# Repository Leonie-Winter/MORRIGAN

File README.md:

# MORRIGAN
--- 
## What is Morrigan?

Morrigan stands for 
- **M**obile
- **O**ptimized
- **R**eal-time
- **R**essource 
- **I**nterface
- **G**auge
- **A**nalysis
- **N**etwork

and aims to be a simple-to-use device based on the Raspberry Pi 3 to determine the quality of water using sensors from Gravity.

It measures the `total dissolved solids (TDS)(that are conductive), the dissolved oxygen (DO), the temperature, the pH, and the Turbidity`

---
You will find a build log in the [wiki](https://github.com/Leonie-Winter/MORRIGAN/wiki/build_log)[WIP] to find out how to get started

`/src` includes all files for the actual code and `/models` which includes a custom pcb design and a 3d case

 &nbsp;&nbsp;&nbsp;&nbsp;&nbsp;

--- 

If you are interested in thins such as previous competitions,the costs, and how it works check out the [wiki](https://github.com/Leonie-Winter/MORRIGAN/wiki/)

---

**This project was funded by the Erasmus+ program of the European Union.**
Funded by the European Union. Views and opinions expressed are however those of the author(s) only and do not necessarily reflect those of the European Union or the European Education and Culture Executive Agency (EACEA). Neither the European Union nor EACEA can be held responsible for them.

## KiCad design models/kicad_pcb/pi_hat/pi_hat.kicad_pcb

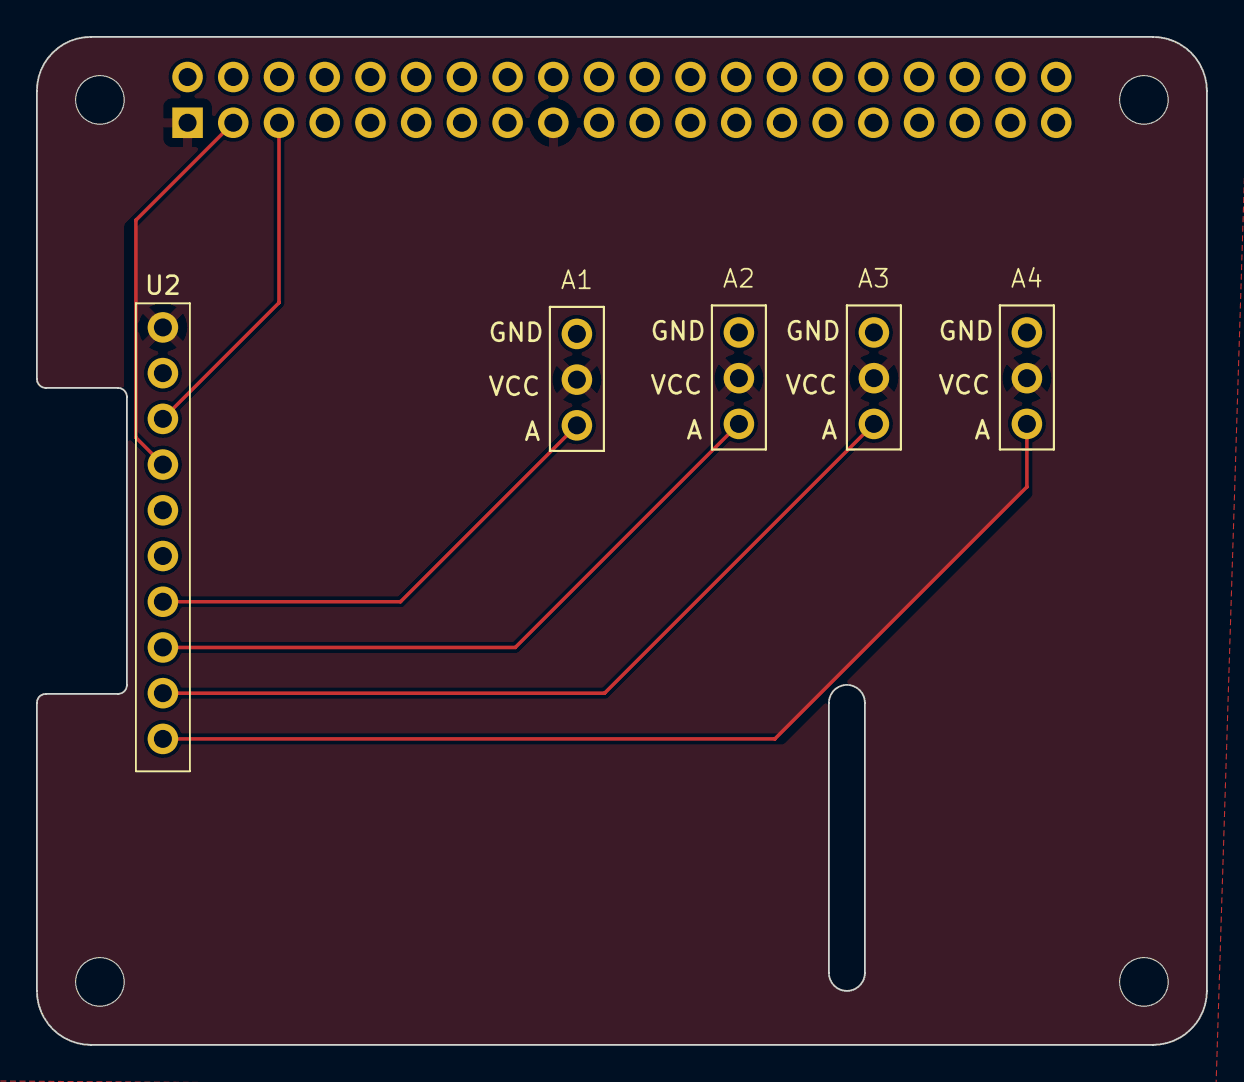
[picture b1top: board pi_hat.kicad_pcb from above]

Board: 2 copper layers, 65.0 x 56.0 mm, 10 parts (1 on the bottom side), 9 nets.

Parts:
A1, A2, A3, A4: analog_Pins
J1: GPIO; PinSocket_2x20_P2.54mm_Vertical
MH1, MH2, MH3, MH4: MountingHole_2.7mm_M2.5
U2: ADS1115

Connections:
+3V3: A1.2 (VCC), A2.2 (VCC), A3.2 (VCC), A4.2 (VCC), J1.1, J1.17, U2.1 (VDD)
+5V: J1.2, J1.4
/GPIO2/SDA1: J1.3, U2.4 (SDA)
/GPIO3/SCL1: J1.5, U2.3 (SCL)
GND: A1.1 (GND), A2.1 (GND), A3.1 (GND), A4.1 (GND), J1.6, J1.9, J1.14, J1.20, J1.25, J1.30, J1.34, J1.39, U2.2 (GND)
unnamed: A1.3 (A), U2.7 (A0)
unnamed: A2.3 (A), U2.8 (A1)
unnamed: A3.3 (A), U2.9 (A2)
unnamed: A4.3 (A), U2.10 (A3)

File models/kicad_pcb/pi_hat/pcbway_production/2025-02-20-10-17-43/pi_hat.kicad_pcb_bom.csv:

Designator,Quantity,Value,Footprint,Package,MPN,DNP,Mount_Type
"A1, A2, A3, A4",4,~,analog_Pins,,,,tht
J1,1,GPIO,PinSocket_2x20_P2.54mm_Vertical,,,,tht
U2,1,~,ADS1115,,,,tht

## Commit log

2025-01-22 files from pi
2025-01-31 Create nothing
2025-01-31 Website
    Added website for displaying data
2025-01-31 backend
2025-02-03 cleaned the fucking repository
2025-02-04 logs
2025-02-06 images
2025-02-08 Cleaned Repo, Fixed Code
2025-02-08 added log function for frontend functionality
2025-02-09 fixed backend using pi
2025-02-09 jufo zeug
2025-02-20 cleaned repository and added sqlite
2025-02-25 Updated Temperature and Turbidity
    Updated Temperature and Turbidity Scripts to reflect new calibrations measurements
2025-02-26 bwaaaa
2025-02-26 added basically everything
2025-02-26 updated some code
2025-02-26 added bajus files
2025-02-26 commants on code
2025-02-26 3D Modell
2025-02-28 final push
2025-04-02 moved theorethical
